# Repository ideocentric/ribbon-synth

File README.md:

# absonus — Ribbon Synthesizer

A touch-controlled FM ribbon synthesizer built on the [Electrosmith Daisy Seed](https://electro-smith.com/products/daisy-seed) platform. Pitch is controlled by a 150mm soft-pot ribbon sensor; expression by a force-sensitive resistor. A panel of knobs and switches shapes the FM synthesis, distortion, filter, tremolo, and reverb.

## Repository Structure

```
absonus/
├── firmware/
│   ├── absonus/          Main firmware (C++ / CMake, libDaisy + DaisySP)
│   ├── sensor-test/      Utility firmware — reads all panel inputs over serial
│   ├── libDaisy/         Daisy hardware library (git submodule)
│   └── DaisySP/          DSP library (git submodule)
│
├── hardware/
│   ├── enclosure/        FreeCAD / DXF / STL files for the enclosure and drill templates
│   ├── pcb/
│   │   ├── absonus-v0.2/ KiCad schematic and PCB layout (current)
│   │   ├── battery-clamp/ 3D-printable clamp for the 18650 battery holder
│   │   └── library/      KiCad component libraries (symbols + footprints)
│   └── testing-panel/    Laser-cut test panel drawings
│
├── bom/
│   ├── pcb-assembly-bom.csv    JLCPCB assembly BOM for the main PCB
│   └── sourced-components.md   Hand-sourced components (pots, sensors, enclosure, etc.)
│
├── docs/
│   ├── design-notes.md         Hardware layout and component design notes
│   ├── firmware-architecture.md Signal chain, module reference, pin mapping
│   └── datasheets/             Component datasheets (FSR, SoftPot, LS18-P, etc.)
│
├── assets/               Photos, renders (to be added)
│
└── archive/
    ├── firmware/         Earlier prototype sketches (fm, fm-chorus, tremor, sensor-test)
    └── hardware/         Earlier PCB revisions (pcb-v0.1, lipo-charger-booster, power-supply)
```

## Documentation

- [Firmware Architecture](docs/firmware-architecture.md) — signal chain, DSP modules, pin mapping, portamento times
- [Design Notes](docs/design-notes.md) — panel layout, Daisy Seed pin assignments, component selection notes
- [Sourced Components BOM](bom/sourced-components.md) — hand-sourced parts with supplier links
- [PCB Assembly BOM](bom/pcb-assembly-bom.csv) — JLCPCB SMT assembly BOM for the main board

## Build

Native C++ built with CMake against libDaisy + DaisySP, which are included as git submodules:

```bash
git submodule update --init --recursive        # first time only
cd firmware/absonus
cmake -B build -DCMAKE_BUILD_TYPE=Release && cmake --build build
cmake --build build --target program-dfu       # hold BOOT, tap RESET, then flash
```

See [`firmware/README.md`](firmware/README.md) for prerequisites, the ST-Link flashing path, and the serial plotter; [`docs/clion-hardware-workflow.md`](docs/clion-hardware-workflow.md) walks through build/flash/debug in CLion.

## Hardware Verification

Before troubleshooting from audio output, flash `firmware/sensor-test/` to the Daisy Seed immediately after assembly. It reads every pot, switch, force sensor, and soft-pot and streams their normalized values over serial (100 ms interval). Plot them with `firmware/sensor-test/plot_sensors.py` (or any serial monitor) to confirm each input responds correctly and is wired to the right pin before loading the main firmware.

## Acknowledgments

Portions of the firmware refactor, documentation, and repository organization were developed with the assistance of [Claude Code](https://claude.com/claude-code) (Anthropic).

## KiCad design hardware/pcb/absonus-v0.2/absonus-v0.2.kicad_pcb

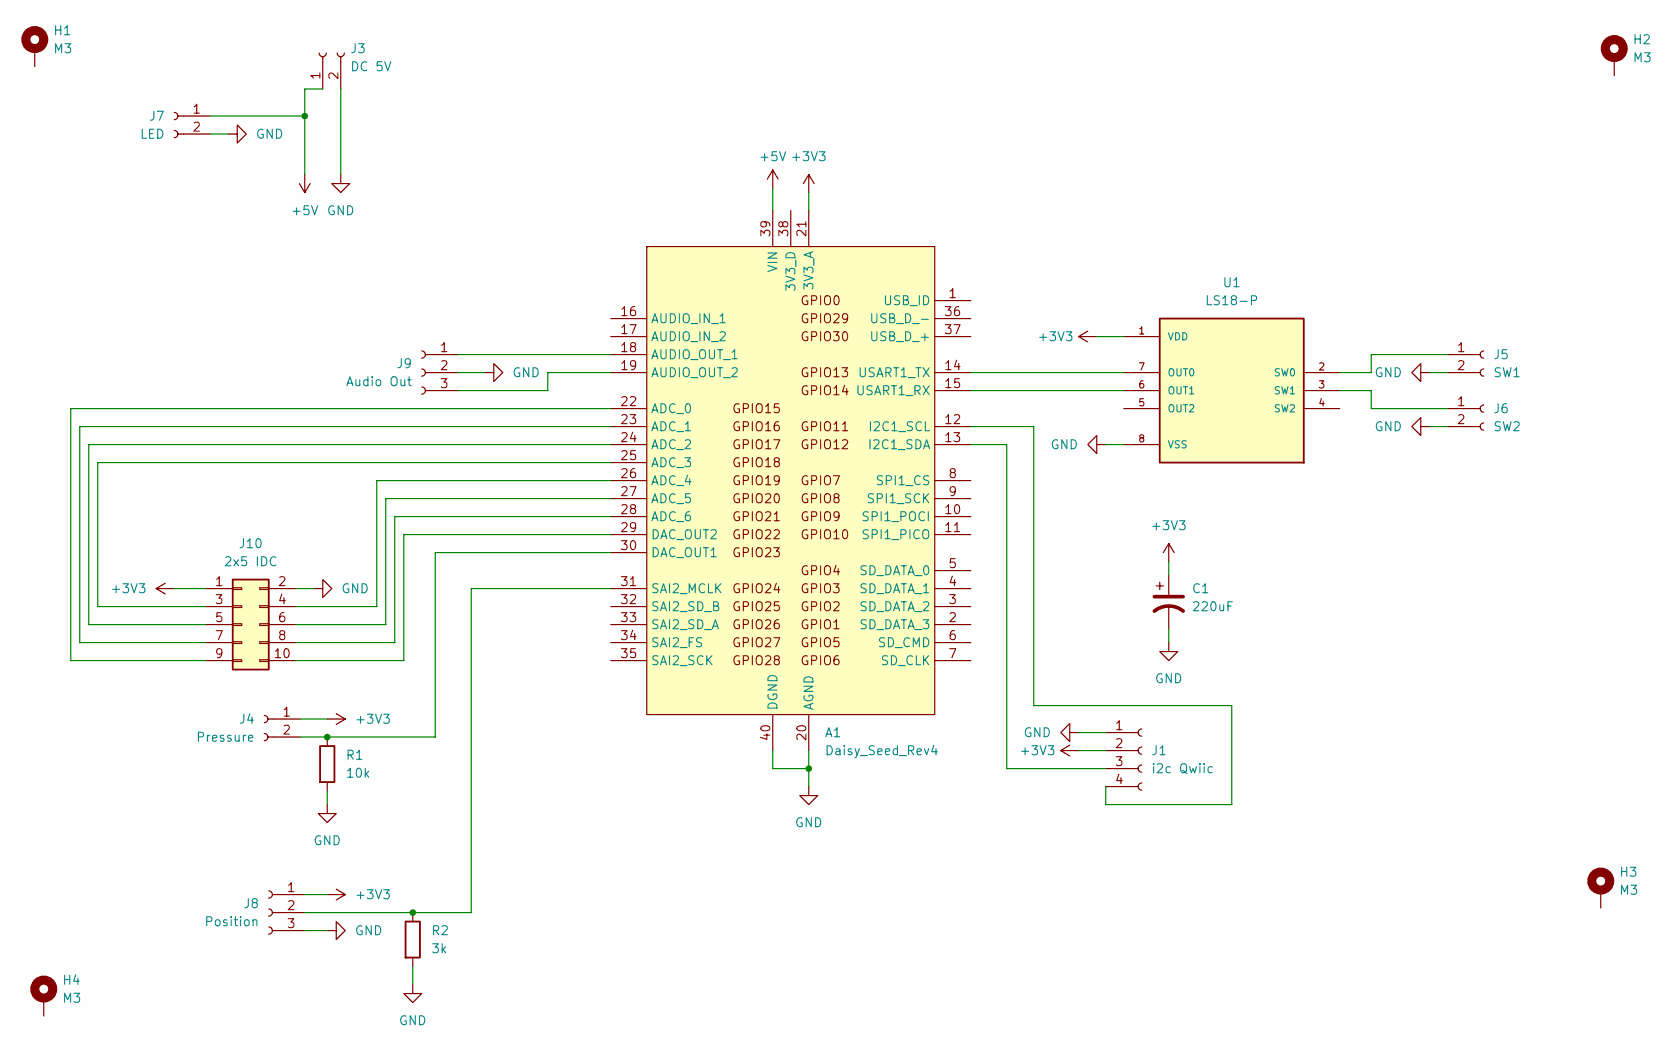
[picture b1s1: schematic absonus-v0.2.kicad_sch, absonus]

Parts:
A1: Daisy_Seed_Rev4; Electrosmith_Daisy_Seed; LCSC Part # C2897383
C1: 220uF; CP_Elec_5x5.4; LCSC Part # C3337
H1, H2, H3, H4: M3; MountingHole_3.2mm_M3
J1: i2c Qwiic; JST_SH_SM04B-SRSS-TB_1x04-1MP_P1.00mm_Horizontal; LCSC Part # C160404
J3: DC 5V; JST_XH_B2B-XH-A_1x02_P2.50mm_Vertical; LCSC Part # C158012
J4: Pressure; JST_XH_B2B-XH-A_1x02_P2.50mm_Vertical; LCSC Part # C158012
J5: SW1; JST_XH_B2B-XH-A_1x02_P2.50mm_Vertical; LCSC Part # C158012
J6: SW2; JST_XH_B2B-XH-A_1x02_P2.50mm_Vertical; LCSC Part # C158012
J7: LED; JST_XH_B2B-XH-A_1x02_P2.50mm_Vertical; LCSC Part # C158012
J8: Position; JST_XH_B3B-XH-A_1x03_P2.50mm_Vertical; LCSC Part # C144394
J9: Audio Out; JST_XH_B3B-XH-A_1x03_P2.50mm_Vertical; LCSC Part # C144394
J10: 2x5 IDC; IDC-Header_2x05_P2.54mm_Vertical; LCSC Part # C4749194
R1: 10k; R_0603_1608Metric; LCSC Part # C15401
R2: 3k; R_0201_0603Metric; LCSC Part # C4211
U1: LS18-P; DIP787W45P254L927H533Q8; PARTREV March 2023; LCSC Part # C5289485

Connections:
+3V3: A1.21 (3V3_A), C1.1, J1.2, J4.1, J8.1, J10.1, U1.1 (VDD)
+5V: A1.39 (VIN), J3.1, J7.1
GND: A1.20 (AGND), A1.40 (DGND), C1.2, J1.1, J3.2, J5.2, J6.2, J7.2, J8.3, J9.2, J10.2, R1.2, R2.2, U1.8 (VSS)
unnamed: A1.22 (ADC_0), J10.9
unnamed: A1.23 (ADC_1), J10.7
unnamed: A1.24 (ADC_2), J10.5
unnamed: A1.25 (ADC_3), J10.3
unnamed: A1.26 (ADC_4), J10.4
unnamed: A1.27 (ADC_5), J10.6
unnamed: A1.28 (ADC_6), J10.8
unnamed: A1.18 (AUDIO_OUT_1), J9.1
unnamed: A1.19 (AUDIO_OUT_2), J9.3
unnamed: A1.30 (DAC_OUT1), J4.2, R1.1
unnamed: A1.29 (DAC_OUT2), J10.10
unnamed: A1.12 (I2C1_SCL), J1.4
unnamed: A1.13 (I2C1_SDA), J1.3
unnamed: A1.31 (SAI2_MCLK), J8.2, R2.1
unnamed: A1.15 (USART1_RX), U1.6 (OUT1)
unnamed: A1.14 (USART1_TX), U1.7 (OUT0)
unnamed: J5.1, U1.2 (SW0)
unnamed: J6.1, U1.3 (SW1)

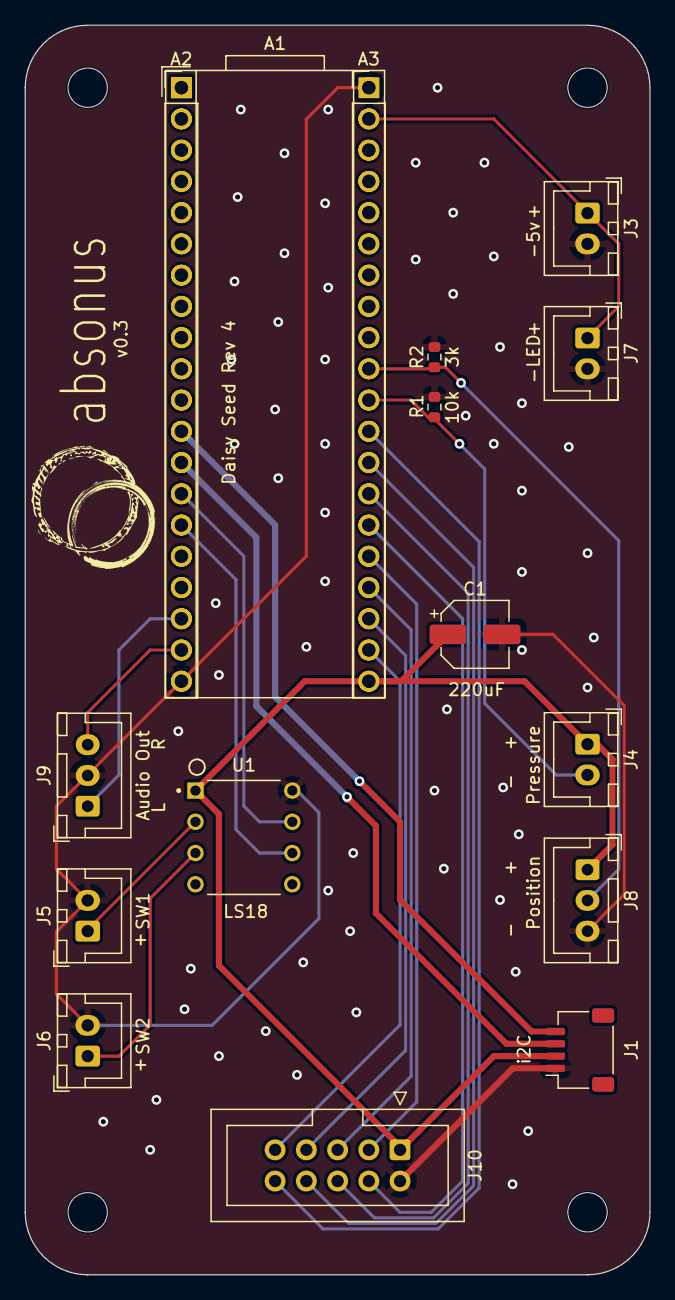
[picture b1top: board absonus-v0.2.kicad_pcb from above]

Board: 2 copper layers, 50.8 x 101.6 mm, 20 parts (0 on the bottom side), 21 nets.

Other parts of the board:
A2, A3: PinHeader_1x20_P2.54mm_Vertical

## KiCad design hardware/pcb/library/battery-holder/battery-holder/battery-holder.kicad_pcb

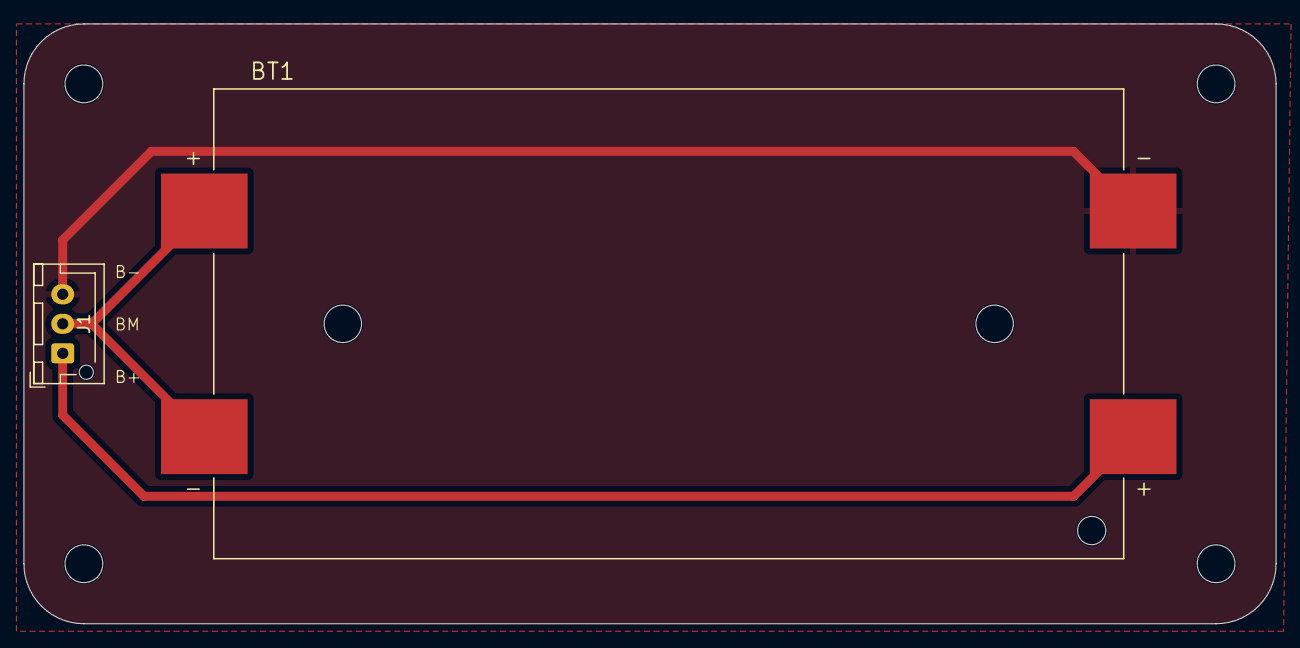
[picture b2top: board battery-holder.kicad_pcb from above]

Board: 2 copper layers, 106.0 x 50.8 mm, 6 parts (0 on the bottom side), 3 nets.

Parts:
BT1: 1048P; BAT_1048P_No_Mount_holes
H1, H2, H3, H4: MountingHole; MountingHole_3.2mm_M3
J1: JST-XH; JST_XH_B3B-XH-AM_1x03_P2.50mm_Vertical

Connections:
+BATT: BT1.P2, J1.1
-BATT: BT1.N1, J1.3
VBUS: BT1.N2, BT1.P1, J1.2

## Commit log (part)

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2023-10-02 added components
2023-10-03 completed working code with exception of noise or reverb
2023-10-03 cleanup of redundant and obsolete items
2023-10-04 add noise and reverb. set modulation rate to static value. changed layout of knobs
2023-10-04 updated design notes
2023-10-11 added drawings
2026-04-06 added all components.
2026-04-06 Updated firmware-architecture.md - clean up
2026-04-06 updated name
2026-04-06 Updated KiCAD files to latest version. output PDFs

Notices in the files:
hardware/pcb/absonus-v0.2/absonus-v0.2.kicad_pcb:
License: MIT
